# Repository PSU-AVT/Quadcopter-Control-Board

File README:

Autonomous Vehicles Team
Quadcopter Control Board

v1 (protoboard)

v2 (first pcb) built and found to have no functioning power layer, and the TxD/RxD lines were swapped between the processor and the FTDI serial out. The XBee serial worked correctly.  

v3 (current pcb) modified the clock traces, added a mini-USB connector and 5V-3.3V regulator, fixed the RxD/TxD oops, and repaired the power plane. Hardware successfully deployed.

Built collaboratively by Jenner Hanni (wicker), Camille Huffman Day (squidpie), and Greg Haynes (greghaynes). Huge thanks to Andrew Greenberg, Bart Massey, Chris, and Tim from the Portland State Aerospace Society.

These files use the MIT License.

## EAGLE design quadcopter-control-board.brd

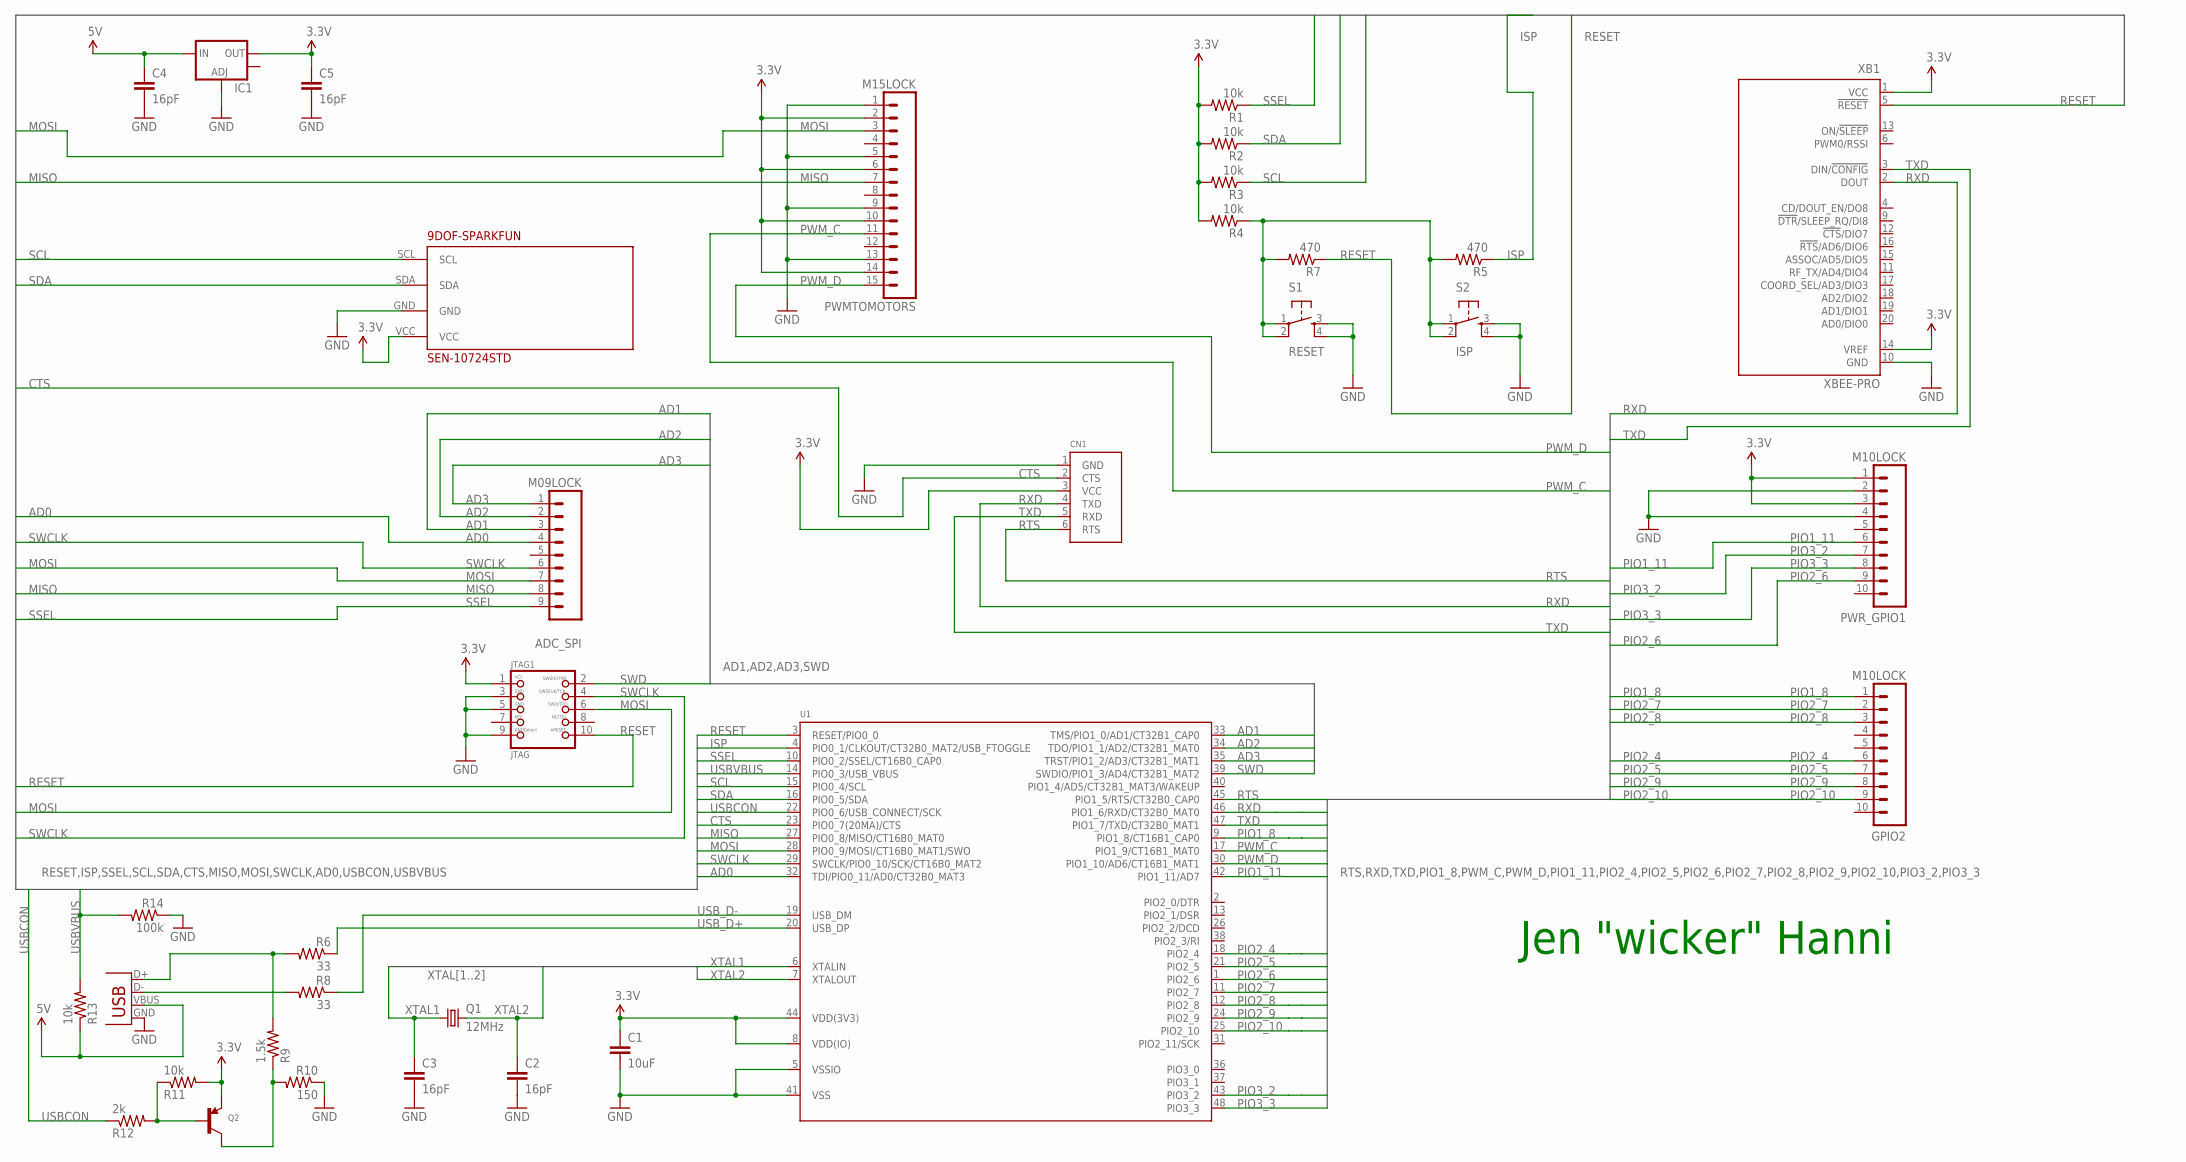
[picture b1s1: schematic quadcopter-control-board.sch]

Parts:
9DOF-SPARKFUN: SEN-10724STD; SPARKFUN-9DOF
ADC_SPI: M09LOCK; 1X09_LOCK
C1: 10uF; 0603-CAP
C2, C3, C4, C5: 16pF; 0603-CAP
CN1: FTDIUSBCABLE; 1X06_ROUND
GPIO2: M10LOCK; 1X10_LOCK
IC1: V_REG_LM1117SOT223; SOT223
JTAG1: JTAG; CORTEXM3_SWD10_MOLEX
PWMTOMOTORS: M15LOCK; 1X15_LOCK
PWR_GPIO1: M10LOCK; 1X10_LOCK
Q1: 12MHz; CTS406
Q2: TRANSISTOR_PNPSOT23-REFLOW; SOT23-R
R1, R2, R3, R4, R11, R13: 10k; 0603-RES
R5, R7: 470; 0603-RES
R6, R8: 33; 0603-RES
R9: 1.5k; 0603-RES
R10: 150; 0603-RES
R12: 2k; 0603-RES
R14: 100k; 0603-RES
S1: RESET; TACTILE_SWITCH_SMD
S2: ISP; TACTILE_SWITCH_SMD
U1: LPC1343_QFP; LQFP48
X1: USB-SMD-NS; USB-MINIB-NOSTOP
XB1: XBEE-PRO

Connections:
3.3V: 9DOF-SPARKFUN.VCC, C1.1, C5.1, CN1.3 (VCC), IC1.2 (OUT), JTAG1.1, PWMTOMOTORS.2, PWMTOMOTORS.6, PWMTOMOTORS.10, PWMTOMOTORS.14, PWR_GPIO1.1, PWR_GPIO1.3, Q2.2 (E), R1.2, R2.2, R3.2, R4.2, R11.2, U1.8 (VDD(IO)), U1.44 (VDD(3V3)), XB1.1 (VCC), XB1.14 (VREF)
5V: C4.1, IC1.3 (IN), R13.1, X1.VBUS
AD0: ADC_SPI.4, U1.32 (TDI/PIO0_11/AD0/CT32B0_MAT3)
AD1: ADC_SPI.3, U1.33 (TMS/PIO1_0/AD1/CT32B1_CAP0)
AD2: ADC_SPI.2, U1.34 (TDO/PIO1_1/AD2/CT32B1_MAT0)
AD3: ADC_SPI.1, U1.35 (TRST/PIO1_2/AD3/CT32B1_MAT1)
CTS: CN1.2 (CTS), U1.23 (PIO0_7(20MA)/CTS)
GND: 9DOF-SPARKFUN.GND, C1.2, C2.2, C3.2, C4.2, C5.2, CN1.1 (GND), IC1.1 (ADJ), JTAG1.3, JTAG1.5, JTAG1.9, PWMTOMOTORS.1, PWMTOMOTORS.5, PWMTOMOTORS.9, PWMTOMOTORS.13, PWR_GPIO1.2, PWR_GPIO1.4, R10.1, R14.1, S1.3, S1.4, S2.3, S2.4, U1.5 (VSSIO), U1.41 (VSS), X1.GND, XB1.10 (GND)
ISP: R5.1, U1.4 (PIO0_1/CLKOUT/CT32B0_MAT2/USB_FTOGGLE)
MISO: ADC_SPI.8, PWMTOMOTORS.7, U1.27 (PIO0_8/MISO/CT16B0_MAT0)
MOSI: ADC_SPI.7, JTAG1.6, PWMTOMOTORS.3, U1.28 (PIO0_9/MOSI/CT16B0_MAT1/SWO)
unnamed: R6.2, R9.2, X1.D+
unnamed: R8.2, X1.D-
unnamed: Q2.3 (C), R9.1, R10.2
unnamed: Q2.1 (B), R11.1, R12.2
unnamed: R4.1, R5.2, R7.2, S1.1, S1.2, S2.1, S2.2
PIO1_8: GPIO2.1, U1.9 (PIO1_8/CT16B1_CAP0)
PIO1_11: PWR_GPIO1.6, U1.42 (PIO1_11/AD7)
PIO2_4: GPIO2.6, U1.18 (PIO2_4)
PIO2_5: GPIO2.7, U1.21 (PIO2_5)
PIO2_6: PWR_GPIO1.9, U1.1 (PIO2_6)
PIO2_7: GPIO2.2, U1.11 (PIO2_7)
PIO2_8: GPIO2.3, U1.12 (PIO2_8)
PIO2_9: GPIO2.8, U1.24 (PIO2_9)
PIO2_10: GPIO2.9, U1.25 (PIO2_10)
PIO3_2: PWR_GPIO1.7, U1.43 (PIO3_2)
PIO3_3: PWR_GPIO1.8, U1.48 (PIO3_3)
PWM_C: PWMTOMOTORS.11, U1.17 (PIO1_9/CT16B1_MAT0)
PWM_D: PWMTOMOTORS.15, U1.30 (PIO1_10/AD6/CT16B1_MAT1)
RESET: JTAG1.10, R7.1, U1.3 (RESET/PIO0_0), XB1.5 (!RESET)
RTS: CN1.6 (RTS), U1.45 (PIO1_5/RTS/CT32B0_CAP0)
RXD: CN1.4 (TXD), U1.46 (PIO1_6/RXD/CT32B0_MAT0), XB1.2 (DOUT)
SCL: 9DOF-SPARKFUN.SCL, R3.1, U1.15 (PIO0_4/SCL)
SDA: 9DOF-SPARKFUN.SDA, R2.1, U1.16 (PIO0_5/SDA)
SSEL: ADC_SPI.9, R1.1, U1.10 (PIO0_2/SSEL/CT16B0_CAP0)
SWCLK: ADC_SPI.6, JTAG1.4, U1.29 (SWCLK/PIO0_10/SCK/CT16B0_MAT2)
SWD: JTAG1.2, U1.39 (SWDIO/PIO1_3/AD4/CT32B1_MAT2)
TXD: CN1.5 (RXD), U1.47 (PIO1_7/TXD/CT32B0_MAT1), XB1.3 (DIN/!CONFIG)
USBCON: R12.1, U1.22 (PIO0_6/USB_CONNECT/SCK)
USBVBUS: R13.2, R14.2, U1.14 (PIO0_3/USB_VBUS)
USB_D+: R6.1, U1.20 (USB_DP)
USB_D-: R8.1, U1.19 (USB_DM)
XTAL1: C3.1, Q1.1, U1.6 (XTALIN)
XTAL2: C2.1, Q1.3 (2), U1.7 (XTALOUT)

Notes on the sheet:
Jen "wicker" Hanni

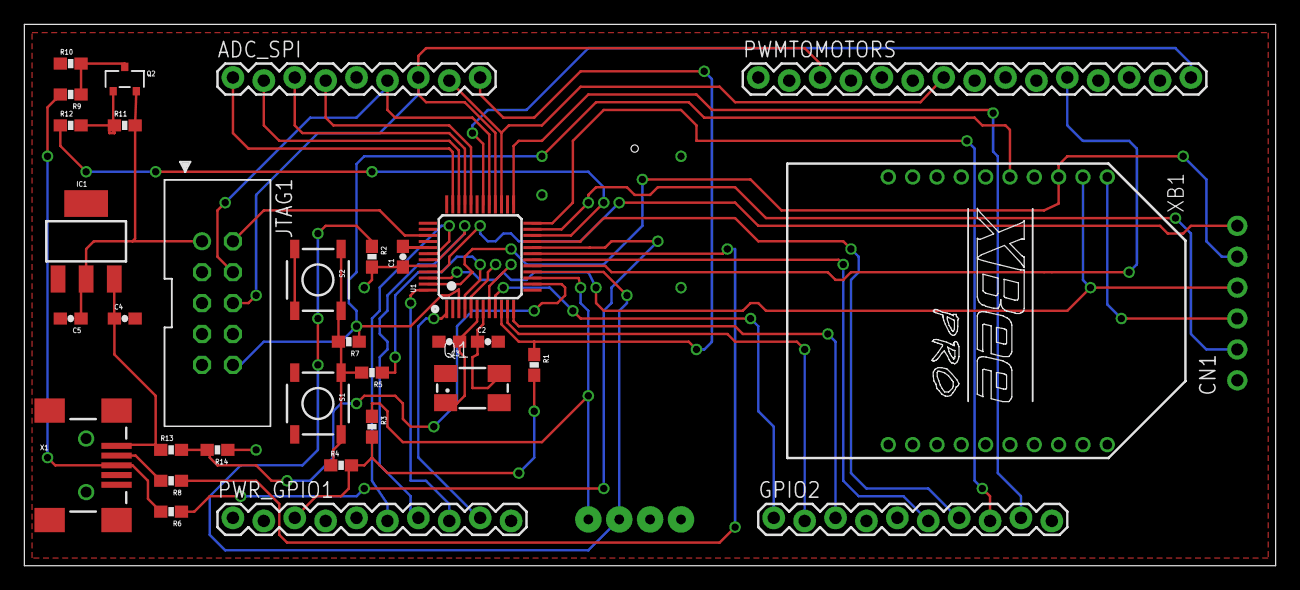
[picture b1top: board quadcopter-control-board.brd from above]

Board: 4 copper layers, 102.8 x 44.5 mm, 34 parts (0 on the bottom side), 44 nets.

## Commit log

2012-03-15 First commit.
2012-05-01 Laid it out from scratch, everything but 9DOF and serial/pwm headers is in the schematic.
2012-05-04 Removed USB as per design review.
2012-05-05 Added 2x5 standard 0.05" SWD connector.
2012-05-05 All serial, GPIO, power pins on nets. Layout in schematic looks good. No error check yet.
2012-05-05 All errors handled, nets verified. Ready for layout.
2012-05-05 I have no idea what I'm doing with this layout process.
2012-05-05 Made 9DOF footprint, added it. Started board layout.
2012-05-05 PWM, JTAG, 9DOF mostly laid out.
2012-05-06 Reworked the header pins to make layout more compact.
2012-05-06 Better layout, reworked headers. Half-laid out.
2012-05-06 All traces linked! Needs clearance, overlap issues resolved.
2012-05-08 Board layout finished, ERC good. DRC throwing layer setup errors for GND/VCC.
2012-05-08 Image of PCB layout, needs design review.
2012-05-15 Needs buses.
2012-05-15 Add ground, 3.3V layers with polygons. Requires ripup; and start over.
2012-05-15 Replaced DB9 with FTDI. Moved crystal caps closer to microprocessor. Vias 0.013 drill size. Added top ground fill. Isolation distance 0.05 inch.
2012-05-17 Add XTAL bus. Needs rest of buses, move components, enlarge area.
2012-05-17 Reconnect all lines, place ground vias. Ready to ship to Mr PCB Man.
2012-05-18 Place buses on SCH. Board and schematic consistent. Pass ERC and DRC. Ready to fab.
2012-05-18 Add PNGs.
2012-05-18 Thank Andrew in the README.
2012-06-05 Lay out board to fix ground plane issues.
2012-06-21 Modify oscillator layout so XTAL1 and XTAL2 are symmetrical, closer, more direct.
2012-07-04 Photo of top layer of newly fabricated board.
2012-08-09 Fix RxD,TxD. Add 5 to 3.3V reg. Add mini USB. Passes ERC.
2012-08-09 Fixed up photos into versions.
2012-08-09 Fix RxD and TxD. Add 5 to 3.3V regulator. Add mini USB. Passes ERC.
2012-08-09 Position new main elements, clean up areas and ripup old wires.
2012-08-17 Quadcopter Board v2 is ready to go.
2012-08-17 Gerbers.
2012-08-17 I meant v3. This is v3.
2012-08-17 Adding v3.
2012-08-25 Syncing with the original for posterity.
2012-11-10 Minor trace fixes and parts list.
2013-07-20 Broke out v2 and v3 boards into separate files.
2013-07-21 Fixed typo.

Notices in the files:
parts and their libraries:
SparkFun-Aesthetics: Licensing: CC v3.0 Share-Alike You are welcome to use this library for commercial purposes.
